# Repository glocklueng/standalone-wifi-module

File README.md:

Standalone Wifi IoT Module 
--------------------------

ESP8266 module with battery charge circuit and some basic IO.

*v1 Status*  
- ordered the board Super Swift on 15 Sep 2015
- ordered all the Digikey parts on 15 Sep 2015

This product uses the [ESP8266 ESP-12E](http://www.electrodragon.com/product/esp-12e-esp8266-wifi-board/).

[Schematic PDF](standalone-v1-schematic.pdf)

### Bill of Materials

|RefDes|Qty|Description|Mfr|Mfr P/N|Dist|Dist P/N|
|------|---|-----------|---|-------|----|--------|
|C1,C2|2|CAP CER 4.7UF 10V 20% X5R 0603|Murata|GRM188R61A475ME15D|Digikey|490-10478-1-ND|
|C3|1|CAP CER 10UF 10V 10% X5R 0603|Murata|GRM188R61A106KE69D|Digikey|490-10474-1-ND|
|D1,D4|2|LED RED DIFFUSED 0603 SMD|OSRAM Opto|LS L296-P2Q2-1-Z|Digikey|475-2761-1-ND|
|D2|1|LED SMARTLED AMBER 615NM 0603|OSRAM Opto|LA L296-Q2R2-1-Z|Digikey|475-2712-1-ND|
|D3|1|LED PURE GREEN 0603 SMD|Stanley|BG1111C-TR|Digikey|404-1005-1-ND|
|J1|1|MICRO B USB RECEPTACLE SMT W/ STUDS|Hirose|ZX62D-B-5P8|Digikey|H11610CT-ND|
|J2|1|CONN HEADER PH SIDE 2POS 2MM SMD|JST|S2B-PH-SM4-TB(LF)(SN)|Digikey|455-1749-1-ND|
|L1|1|FIXED IND 4.7UH 600MA 344.5 MOHM|Taiyo|BRC2012T4R7MD|Digikey|587-2907-1-ND|
|R4|1|RES SMD 2K OHM 1% 1/10W 0402|Panasonic|ERJ-2RKF2001X|Digikey|P2.00KLCT-ND|
|R5,R7-R10|5|RES SMD 10K OHM 1% 1/10W 0402|Panasonic|ERJ-2RKF1002X|Digikey|P10.0KLCT-ND|
|R1-R3|3|RES SMD 150 OHM 1% 1/10W 0402|Panasonic|ERJ-2RKF1500X|Digikey|P150LCT-ND|
|RESET,GPIO0|2|SWITCH TACTILE SPST-NO 0.05A 24V|TE Conn|FSMSM|Digikey|450-1140-ND|
|U1|1|ESP8266 ESP-12E WIFI MODULE|ESP8266|ESP-12E|Electrodragon|NWI1040|
|U2|1|IC LI-ION/LI-POLY CTRLR 10MSOP|Microchip|MCP73833-AMI/UN|Digikey|MCP73833-AMI/UN-ND|
|U3|1|IC REG BST 5V 295MA SYNC SOT-25|Torex|XC9140A501MR-G|Digikey|893-1181-1-ND|
|U4|1|IC REG LDO 3.3V 0.25A SOT23A-3|Microchip|MCP1703T-3302E/CB|Digikey|MCP1703T-3302E/CBCT-ND|

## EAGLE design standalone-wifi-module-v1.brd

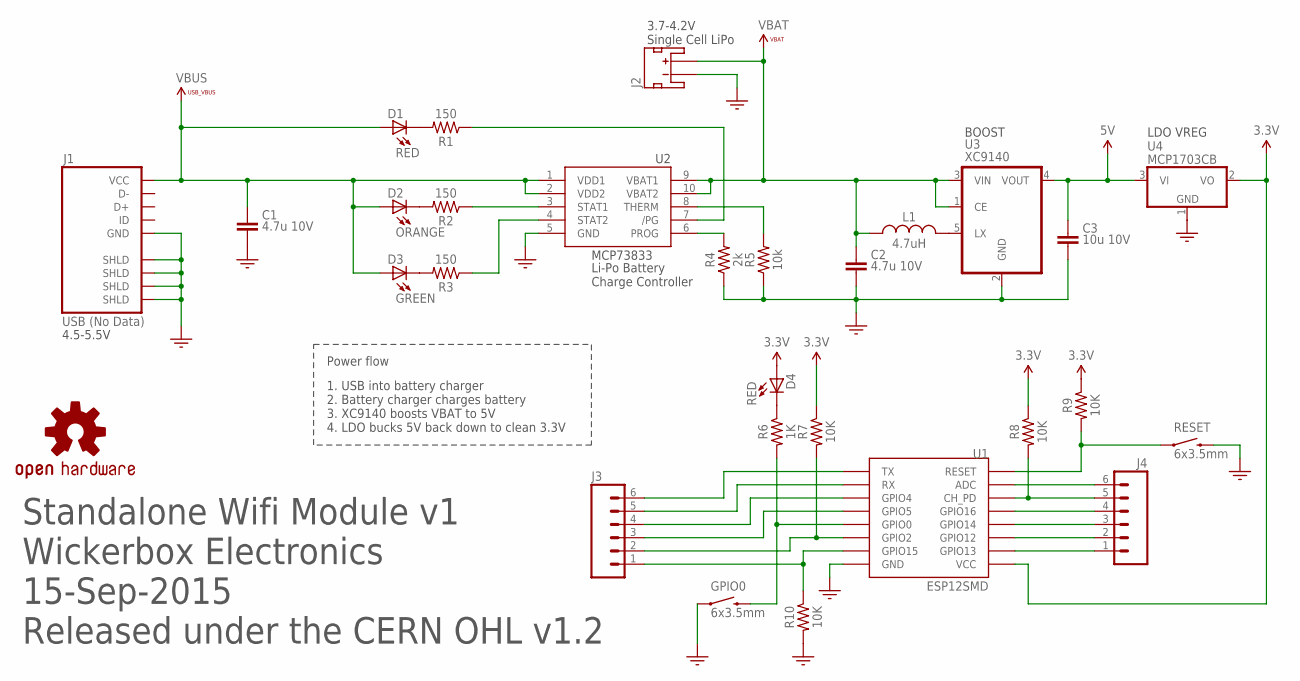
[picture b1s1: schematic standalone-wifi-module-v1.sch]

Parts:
C1: 4.7u 10V; RLC-0805
C2: 4.7u 10V; RLC-0603
C3: 10u 10V; RLC-0603
D1, D4: RED; LED0603
D2: ORANGE; LED0603
D3: GREEN; LED0603
GPIO0: 6x3.5mm; TACTILE-SWITCH-1101NE
J1: USB (No Data); ZX62D-B-5P8
J2: JST_2MM_MALE; JST-2-SMD
J3, J4: M06LOCK_LONGPADS; 1X06_LOCK_LONGPADS
L1: 4.7uH; RLC-0805
R1, R2, R3: 150; RLC-0402
R4: 2k; RLC-0402
R5: 10k; RLC-0402
R6: 1K; RLC-0402
R7, R8, R9, R10: 10K; RLC-0402
RESET: 6x3.5mm; TACTILE-SWITCH-1101NE
U1: ESP12SMD; ESP12_SMD
U2: MCP73833-UN; MSOP10
U3: XC9140; SOT-25
U4: MCP1703CB; SOT23
U$2: OSHW_LOGO_SYMM; OSHW_LOGO_MED_SYM

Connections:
3.3V: D4.A, R7.1, R8.1, R9.1, U1.VCC, U4.2 (VO)
5V: C3.2 (1), U3.4 (VOUT), U4.3 (VI)
!RESET: R9.2, RESET.1, U1.RESET
ADC: J4.6, U1.ADC
CH_PD: J4.5, R8.2, U1.CH_PD
GND: C1.2, C2.1 (2), C3.1 (2), GPIO0.1, J1.P5 (GND), J1.P$1 (SHLD), J1.P$2 (SHLD), J1.P$3 (SHLD), J1.P$4 (SHLD), J2.1 (-), R4.1, R5.1, R10.2, RESET.2, U1.GND, U2.5 (GND), U3.2 (GND), U4.1 (GND)
GPIO0: GPIO0.2, R6.2, U1.GPIO0
GPIO2: J3.2, R7.2, U1.GPIO2
GPIO4: J3.4, U1.GPIO4
GPIO5: J3.3, U1.GPIO5
GPIO12: J4.2, U1.GPIO12
GPIO13: J4.1, U1.GPIO13
GPIO14: J4.3, U1.GPIO14
GPIO15: J3.1, R10.1, U1.GPIO15
GPIO16: J4.4, U1.GPIO16
unnamed: D4.C, R6.1
unnamed: L1.2, U3.5 (LX)
unnamed: D2.C, R2.2
unnamed: D3.C, R3.2
unnamed: D1.C, R1.2
PG: R1.1, U2.7 (/PG)
PROG: R4.2, U2.6 (PROG)
RX: J3.5, U1.RX
STAT1: R2.1, U2.3 (STAT1)
STAT2: R3.1, U2.4 (STAT2)
THERM: R5.2, U2.8 (THERM)
TX: J3.6, U1.TX
VBAT: C2.2 (1), J2.2 (+), L1.1, U2.9 (VBAT1), U2.10 (VBAT2), U3.1 (CE), U3.3 (VIN)
VBUS: C1.1, D1.A, D2.A, D3.A, J1.P1 (VCC), U2.1 (VDD1), U2.2 (VDD2)

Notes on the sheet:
1. USB into battery charger 2. Battery charger charges battery 3. XC9140 boosts VBAT to 5V 4. LDO bucks 5V back down to clean 3.3V
LDO VREG
Power flow
BOOST
4.5-5.5V
Li-Po Battery Charge Controller
3.7-4.2V Single Cell LiPo
Standalone Wifi Module v1 Wickerbox Electronics 15-Sep-2015 Released under the CERN OHL v1.2

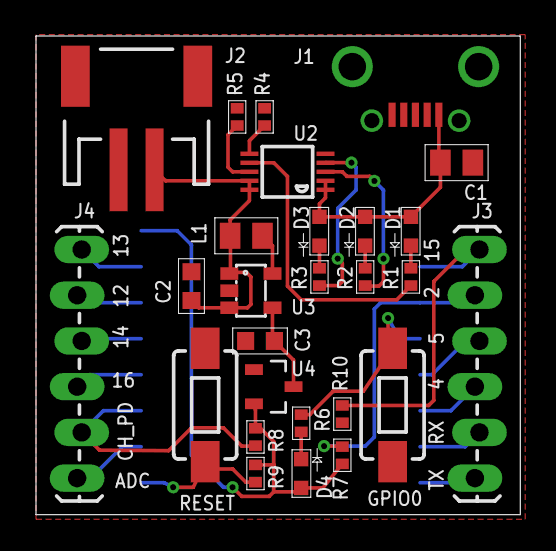
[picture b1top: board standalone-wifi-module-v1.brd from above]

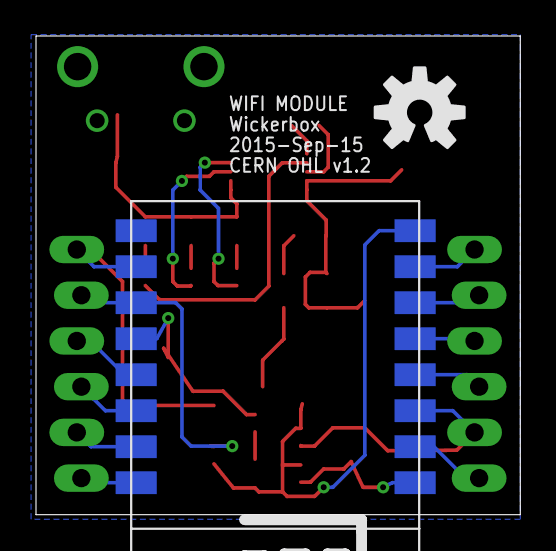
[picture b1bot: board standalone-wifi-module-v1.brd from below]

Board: 2 copper layers, 26.9 x 26.6 mm, 29 parts (2 on the bottom side), 29 nets.

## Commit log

2015-09-15 First board rev ordered.
2015-09-15 Ordered boards from OSH Park, updated full BOM in README.

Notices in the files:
parts and their libraries:
SparkFun-Connectors: Licensing: Creative Commons ShareAlike 4.0 International - https://creativecommons.org/licenses/by-sa/4.0
PatternAgents-Logos: License : http://creativecommons.org/licenses/by-sa/3.0
(Creative Commons 3.0)
